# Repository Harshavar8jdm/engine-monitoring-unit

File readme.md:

# Engine Monitoring Unit (EMU) 🏍️⚡

An open-source, automotive-grade **Engine Monitoring Unit (EMU)** designed to bring real-time engine telemetry and diagnostics to air-cooled single-cylinder motorcycles (such as the Hero Passion Plus) that lack factory instrumentation.

Powered by an **STM32F411CEU6** ARM Cortex-M4 microcontroller, this unit captures vital thermal, electrical, and rotational parameters and displays them on a handlebar-mounted OLED screen—giving riders full visibility over engine health during long highway cruises and touring trips.

---

## 📌 Gallery

| Top 3D Render | Bottom 3D Render |
| :---: | :---: |
|  |  |

---

## 🎯 Motivation & Objectives

Stock commuter motorcycles often lack essential monitoring tools, providing only a basic speedometer and fuel gauge. When pushing small-displacement air-cooled engines on long rides or steep climbs, thermal overload or electrical failure can happen without warning.

This project solves that real-world problem by providing:
1. **Real-time Engine Health Visibility:** Monitoring oil temperature and intake air temperature (IAT) to prevent overheating.
2. **Electrical System Telemetry:** Tracking live battery voltage to monitor stator and regulator/rectifier performance.
3. **Engine Dynamics:** Accurate engine RPM via inductive pulse pickup and wheel speed tracking.
4. **Automotive EMI Immunity:** Designed specifically for high noise/vibration motorcycle chassis environments.
5. **Zero Parasitic Battery Drain:** Tied directly to switched ignition (+12V)—completely powered down when the key is OFF.

---

## 🛠️ Key Technical Specifications

| Parameter | Specification | Description |
| :--- | :--- | :--- |
| **Microcontroller** | STM32F411CEU6 | 100 MHz ARM Cortex-M4, 512KB Flash, 128KB SRAM |
| **Operating Voltage** | 12V DC nominal (Switched) | Powered directly from motorcycle ignition bus |
| **On-board Power** | LMR16006 Buck Converter | 12V → 3.3V Step-down (60V Max $V_{IN}$) |
| **Current Draw** | < 0.6A Operating | 0A Off-state (Zero parasitic load) |
| **PCB Stackup** | 4-Layer | Top (Sig/Pwr) - GND - GND - Bottom (Sig) |
| **Connectors** | Molex Micro-Fit 3.0 | Positive-locking, high-vibration automotive rating |
| **Display Interface** | 0.96" I2C OLED | 4-pin header (3.3V, SDA, SCL, GND) |
| **Debug Interface** | SWD | 4-pin header (3.3V, SWDIO, SWCLK, GND) |

---

## 📐 System Architecture & Schematic Overview

### Circuit Block Summary:
* **Power Supply:** Uses a high-efficiency **LMR16006** synchronous buck regulator stepping down battery voltage to $+3.3\text{V}$ for the MCU and OLED display.
* **Microcontroller Core:** Minimalist STM32F411 layout with external $8\text{ MHz}$ HSE crystal ($Y_1$) and $32.768\text{ kHz}$ LSE crystal ($Y_2$), full decoupling capacitor network ($C_2 - C_7$), and pull-up/down logic for BOOT0/NRST.
* **Inductive RPM Conditioning:** Discrete NPN transistor ($Q_1$) amplifier stage paired with high-speed clamping diodes ($D_4 - D_7$) to cleanly condition high-voltage spark-plug coil inductive pulses into a 3.3V digital square wave.
* **Analog Sensor Inputs:** Resistive voltage dividers and $100\text{ nF}$ filtering capacitors for Oil Temp ($J_3$), Intake Air Temp ($J_4$), and Battery Voltage sensing ($J_2$).
* **Wheel Speed Conditioning:** Digital pulse input circuit with pull-up and low-pass filtering for hall-effect or reed switch wheel sensors ($J_5$).

---

## 📑 PCB Stackup & Layer Breakdown

To withstand the severe Electromagnetic Interference (EMI) generated by motorcycle ignition coils and spark plugs, the PCB utilizes a dedicated **4-layer stackup** with dual continuous internal ground planes.

```text
┌─────────────────────────────────────────────────────────┐
│ Layer 1: Top Layer (FCU)    -> Signals + 3.3V Power     │
├─────────────────────────────────────────────────────────┤
│ Layer 2: Inner 1 (In1)      -> Solid Ground Plane (GND) │
├─────────────────────────────────────────────────────────┤
│ Layer 3: Inner 2 (In2)      -> Solid Ground Plane (GND) │
├─────────────────────────────────────────────────────────┤
│ Layer 4: Bottom Layer (BCU) -> Signal Routing           │
└─────────────────────────────────────────────────────────┘

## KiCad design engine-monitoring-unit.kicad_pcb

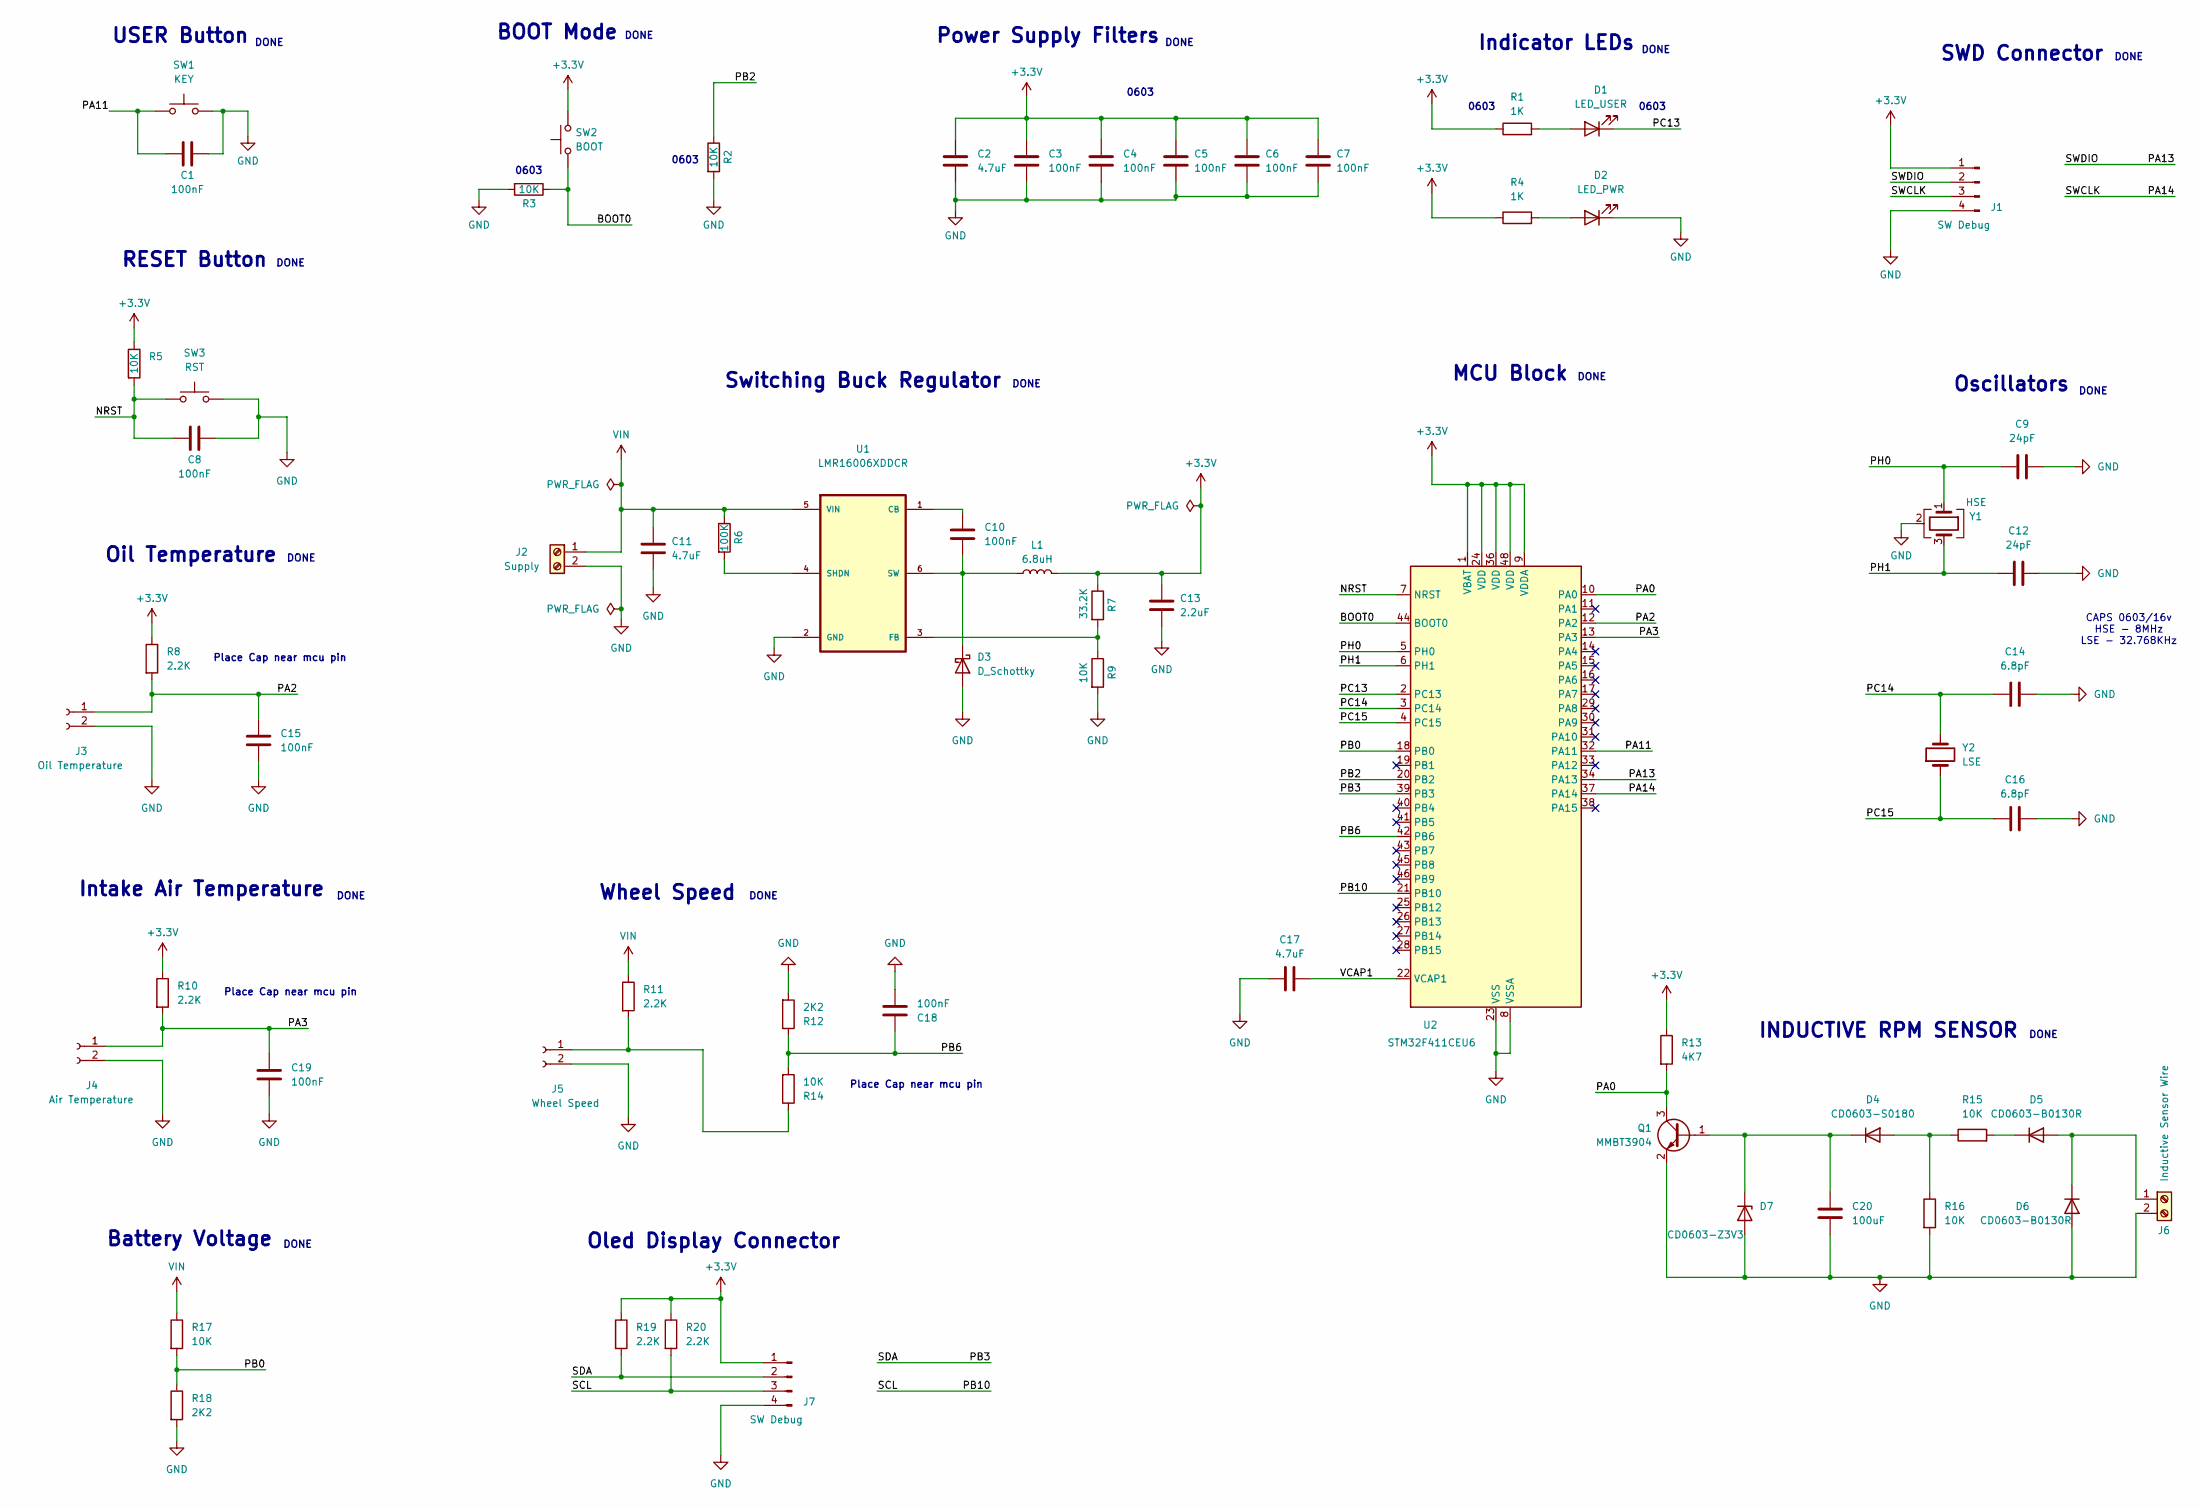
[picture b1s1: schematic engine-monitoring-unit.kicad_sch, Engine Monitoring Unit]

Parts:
C1, C3, C4, C5, C6, C7, C8, C10, C15, C18, C19: 100nF; C_0603_1608Metric_Pad1.08x0.95mm_HandSolder
C2, C11, C17: 4.7uF; C_0603_1608Metric_Pad1.08x0.95mm_HandSolder
C9, C12: 24pF; C_0603_1608Metric_Pad1.08x0.95mm_HandSolder
C13: 2.2uF; C_0603_1608Metric_Pad1.08x0.95mm_HandSolder
C14, C16: 6.8pF; C_0603_1608Metric_Pad1.08x0.95mm_HandSolder
C20: 100uF; C_0603_1608Metric_Pad1.08x0.95mm_HandSolder
D1: LED_USER; LED_0603_1608Metric_Pad1.05x0.95mm_HandSolder
D2: LED_PWR; LED_0603_1608Metric_Pad1.05x0.95mm_HandSolder
D3: D_Schottky; POWERDI-123_L2_8-W1_8-LS3_7-RD-1_SS14FP_C894423
D4: CD0603-S0180; D_0603_1608Metric_Pad1.05x0.95mm_HandSolder
D5, D6: CD0603-B0130R; D_0603_1608Metric_Pad1.05x0.95mm_HandSolder
D7: CD0603-Z3V3; D_0603_1608Metric_Pad1.05x0.95mm_HandSolder
J1: SW Debug; PinHeader_1x04_P2.54mm_Vertical
J2: Supply; Molex_Micro-Fit_3.0_43650-0200_1x02_P3.00mm_Horizontal
J3: Oil Temperature; Molex_Micro-Fit_3.0_43650-0200_1x02_P3.00mm_Horizontal
J4: Air Temperature; Molex_Micro-Fit_3.0_43650-0200_1x02_P3.00mm_Horizontal
J5: Wheel Speed; Molex_Micro-Fit_3.0_43650-0200_1x02_P3.00mm_Horizontal
J6: Inductive Sensor Wire; Molex_Micro-Fit_3.0_43650-0200_1x02_P3.00mm_Horizontal
J7: SW Debug; PinSocket_1x04_P2.54mm_Vertical
L1: 6.8uH; IND-SMD_L4_0-W4_0_NRS4018T_NRS4018T6R8MDGJ_C222881
Q1: MMBT3904; SOT-23
R1, R4: 1K; R_0603_1608Metric_Pad0.98x0.95mm_HandSolder
R2, R3, R5, R9, R14, R15, R16, R17: 10K; R_0603_1608Metric_Pad0.98x0.95mm_HandSolder
R6: 100K; R_0603_1608Metric_Pad0.98x0.95mm_HandSolder
R7: 33.2K; R_0603_1608Metric_Pad0.98x0.95mm_HandSolder
R8, R10, R11, R19, R20: 2.2K; R_0603_1608Metric_Pad0.98x0.95mm_HandSolder
R12, R18: 2K2; R_0603_1608Metric_Pad0.98x0.95mm_HandSolder
R13: 4K7; R_0603_1608Metric_Pad0.98x0.95mm_HandSolder
SW1: KEY; SW_Push_SPST_NO_Alps_SKRK
SW2: BOOT; SW_Push_SPST_NO_Alps_SKRK
SW3: RST; SW_Push_SPST_NO_Alps_SKRK
U1: LMR16006XDDCR; SOT95P280X110-6N
U2: STM32F411CEU6; QFN-48-1EP_7x7mm_P0.5mm_EP5.6x5.6mm
Y1: HSE; CRYSTAL-SMD_4P-L3_2-W2_5-BL_0132M4-8_000F16DTNJL_C19674293
Y2: LSE; CRYSTAL-SMD_L3_2-W1_5-1_3131M32768DT06LL_C5221300

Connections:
+3.3V: C2.1, C3.1, C4.1, C5.1, C6.1, C7.1, C13.1, J1.1, J7.1, L1.2, R1.1, R4.1, R5.1, R7.1, R8.1, R10.1, R13.1, R19.1, R20.1, SW2.2, U2.1 (VBAT), U2.9 (VDDA), U2.24 (VDD), U2.36 (VDD), U2.48 (VDD)
/BOOT0: R3.1, SW2.1, U2.44 (BOOT0)
/NRST: C8.2, R5.2, SW3.1, U2.7 (NRST)
/PA0: Q1.3 (C), R13.2, U2.10 (PA0)
/PA2: C15.1, J3.1, R8.2, U2.12 (PA2)
/PA3: C19.1, J4.1, R10.2, U2.13 (PA3)
/PA11: C1.2, SW1.1, U2.32 (PA11)
/PA13: J1.2, U2.34 (PA13)
/PA14: J1.3, U2.37 (PA14)
/PB0: R17.2, R18.1, U2.18 (PB0)
/PB2: R2.1, U2.20 (PB2)
/PB3: J7.2, R19.2, U2.39 (PB3)
/PB6: C18.1, R12.1, R14.2, U2.42 (PB6)
/PB10: J7.3, R20.2, U2.21 (PB10)
/PC13: D1.1 (K), U2.2 (PC13)
/PC14: C14.1, U2.3 (PC14), Y2.2
/PC15: C16.1, U2.4 (PC15), Y2.1
/PH0: C9.1, U2.5 (PH0), Y1.1
/PH1: C12.1, U2.6 (PH1), Y1.3
/VCAP1: C17.2, U2.22 (VCAP1)
GND: C1.1, C2.2, C3.2, C4.2, C5.2, C6.2, C7.2, C8.1, C9.2, C11.2, C12.2, C13.2, C14.2, C15.2, C16.2, C17.1, C18.2, C19.2, C20.2, D2.1 (K), D3.2 (A), D6.2 (A), D7.2 (A), J1.4, J2.2, J3.2, J4.2, J5.2, J6.2, J7.4, Q1.2 (E), R2.2, R3.2, R9.2, R12.2, R16.2, R18.2, SW1.2, SW3.2, U1.2 (GND), U2.8 (VSSA), U2.23 (VSS), U2.35 (VSS), U2.47 (VSS), U2.49 (VSS), Y1.2 (G), Y1.4 (G)
unnamed: D1.2 (A), R1.2
unnamed: D2.2 (A), R4.2
unnamed: C10.2, D3.1 (K), L1.1, U1.6 (SW)
unnamed: D4.2 (A), R15.1, R16.1
unnamed: C20.1, D4.1 (K), D7.1 (K), Q1.1 (B)
unnamed: D5.2 (A), D6.1 (K), J6.1
unnamed: D5.1 (K), R15.2
unnamed: J5.1, R11.2, R14.1
unnamed: C10.1, U1.1 (CB)
unnamed: R7.2, R9.1, U1.3 (FB)
unnamed: R6.2, U1.4 (SHDN)
VIN: C11.1, J2.1, R6.1, R11.1, R17.1, U1.5 (VIN)

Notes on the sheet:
Indicator LEDs
Place Cap near mcu pin
DONE
Battery Voltage
INDUCTIVE RPM SENSOR
CAPS 0603/16v HSE - 8MHz LSE - 32.768KHz
SWD Connector
Intake Air Temperature
Power Supply Filters
Oil Temperature
0603
Oscillators
USER Button
BOOT Mode
Switching Buck Regulator
Wheel Speed
Oled Display Connector
MCU Block
RESET Button

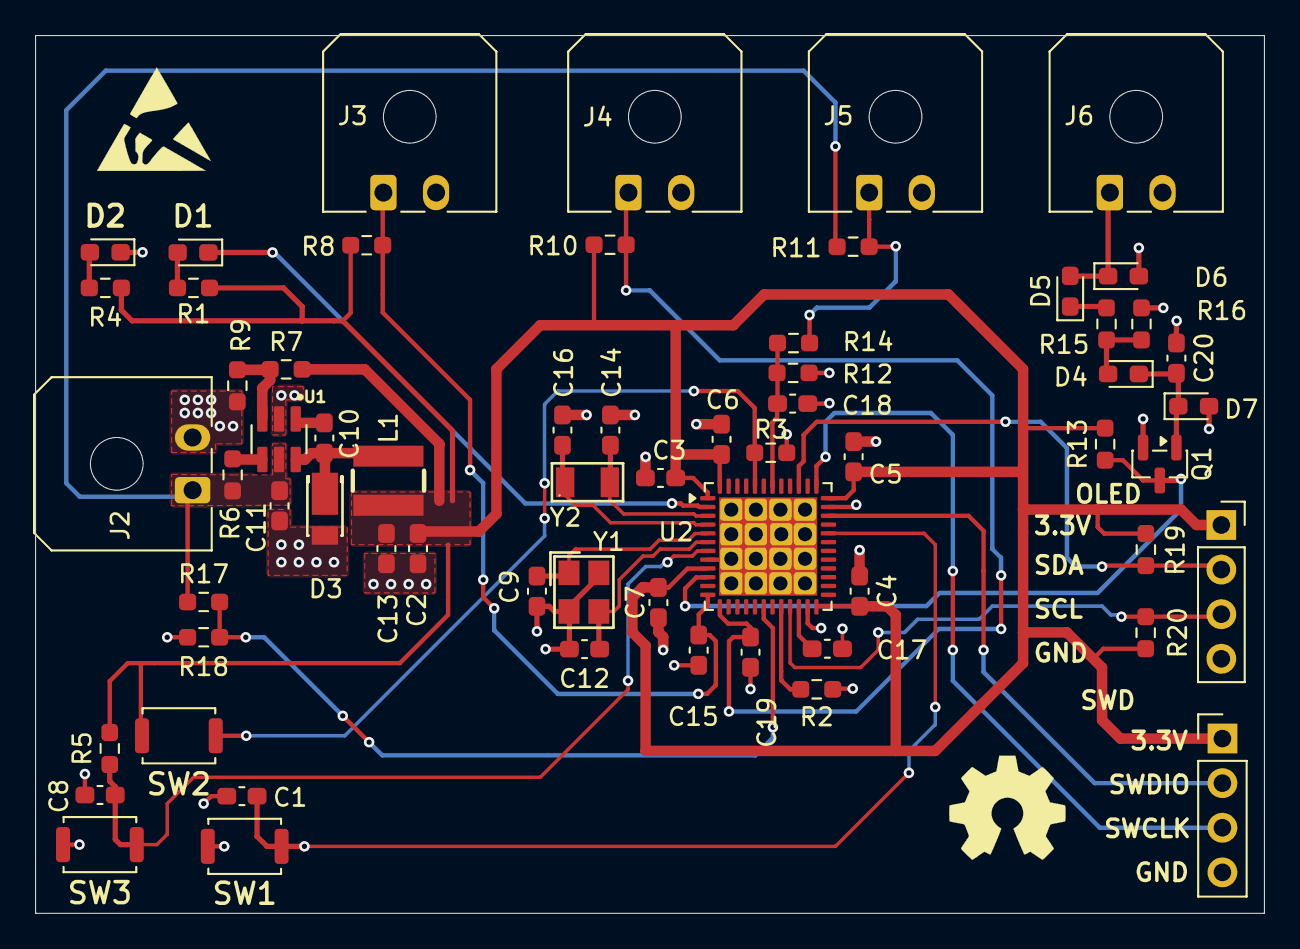
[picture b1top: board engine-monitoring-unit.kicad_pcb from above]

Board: 4 copper layers, 70.0 x 50.0 mm, 63 parts (0 on the bottom side), 33 nets.

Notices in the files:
readme.md:
License: MIT
